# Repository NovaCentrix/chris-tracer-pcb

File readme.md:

# The TraceR 

## A Module for Simulating Conductive Ink PCB Traces

## Revisions

### Version 2

* Digipot power supply from from 3.3 to 5, in order to reduce the wiper
  resistance further (see the datasheet). This means the addition of
  level translator for the MISO signal into the MCU. 

* The digipot SDO pin is open drain. Added pullup resistors on each one.

* Assembly of modules onto v1 board was difficult. And the whole assembly 
  needs to be thinner so two modules can be installed adjacent to each
  other (relates to the pin header spacing on the main board). Gave up
  on the idea of avoiding a board cutout. Re-routing of signals, and
  made the board just slightly larger (mostly taller) to allow for the
  required cutout.

* Changed PCB thickness from 1.6 to 1.0 mm.

* Found some tiny buttons (about the same size as those on the Tiny 2040
  module) and put them at the top corners. This will allow the user to
  change resistance values without using the serial port.

### Version 1

First release. 

## Observations

Before I forget, here are some thoughts to consider if there ever is
going to be a version 3.

* Make D1/D2 larger, since that package is nearly impossible to hand
  solder. Or...

* Make the transistor and resistor packages smaller and reflow rather
  than hand solder. Also, Digipots are available in a smaller package:
    * TSSOP-24 package 7.8 x 4.4 mm 
    * SOIC-24W 15.4 x 7.5 mm (currently used)

* Look carefully at the Adafruit Qt Py RP2040 module. It looks smaller,
  has a smaller and well-defined required cutout and mechanical
  drawings. Fewer pins.

* Save even more space my tossing the module concept and building the
  RP2040 board and the OLED module directly on the TraceR's PCB.

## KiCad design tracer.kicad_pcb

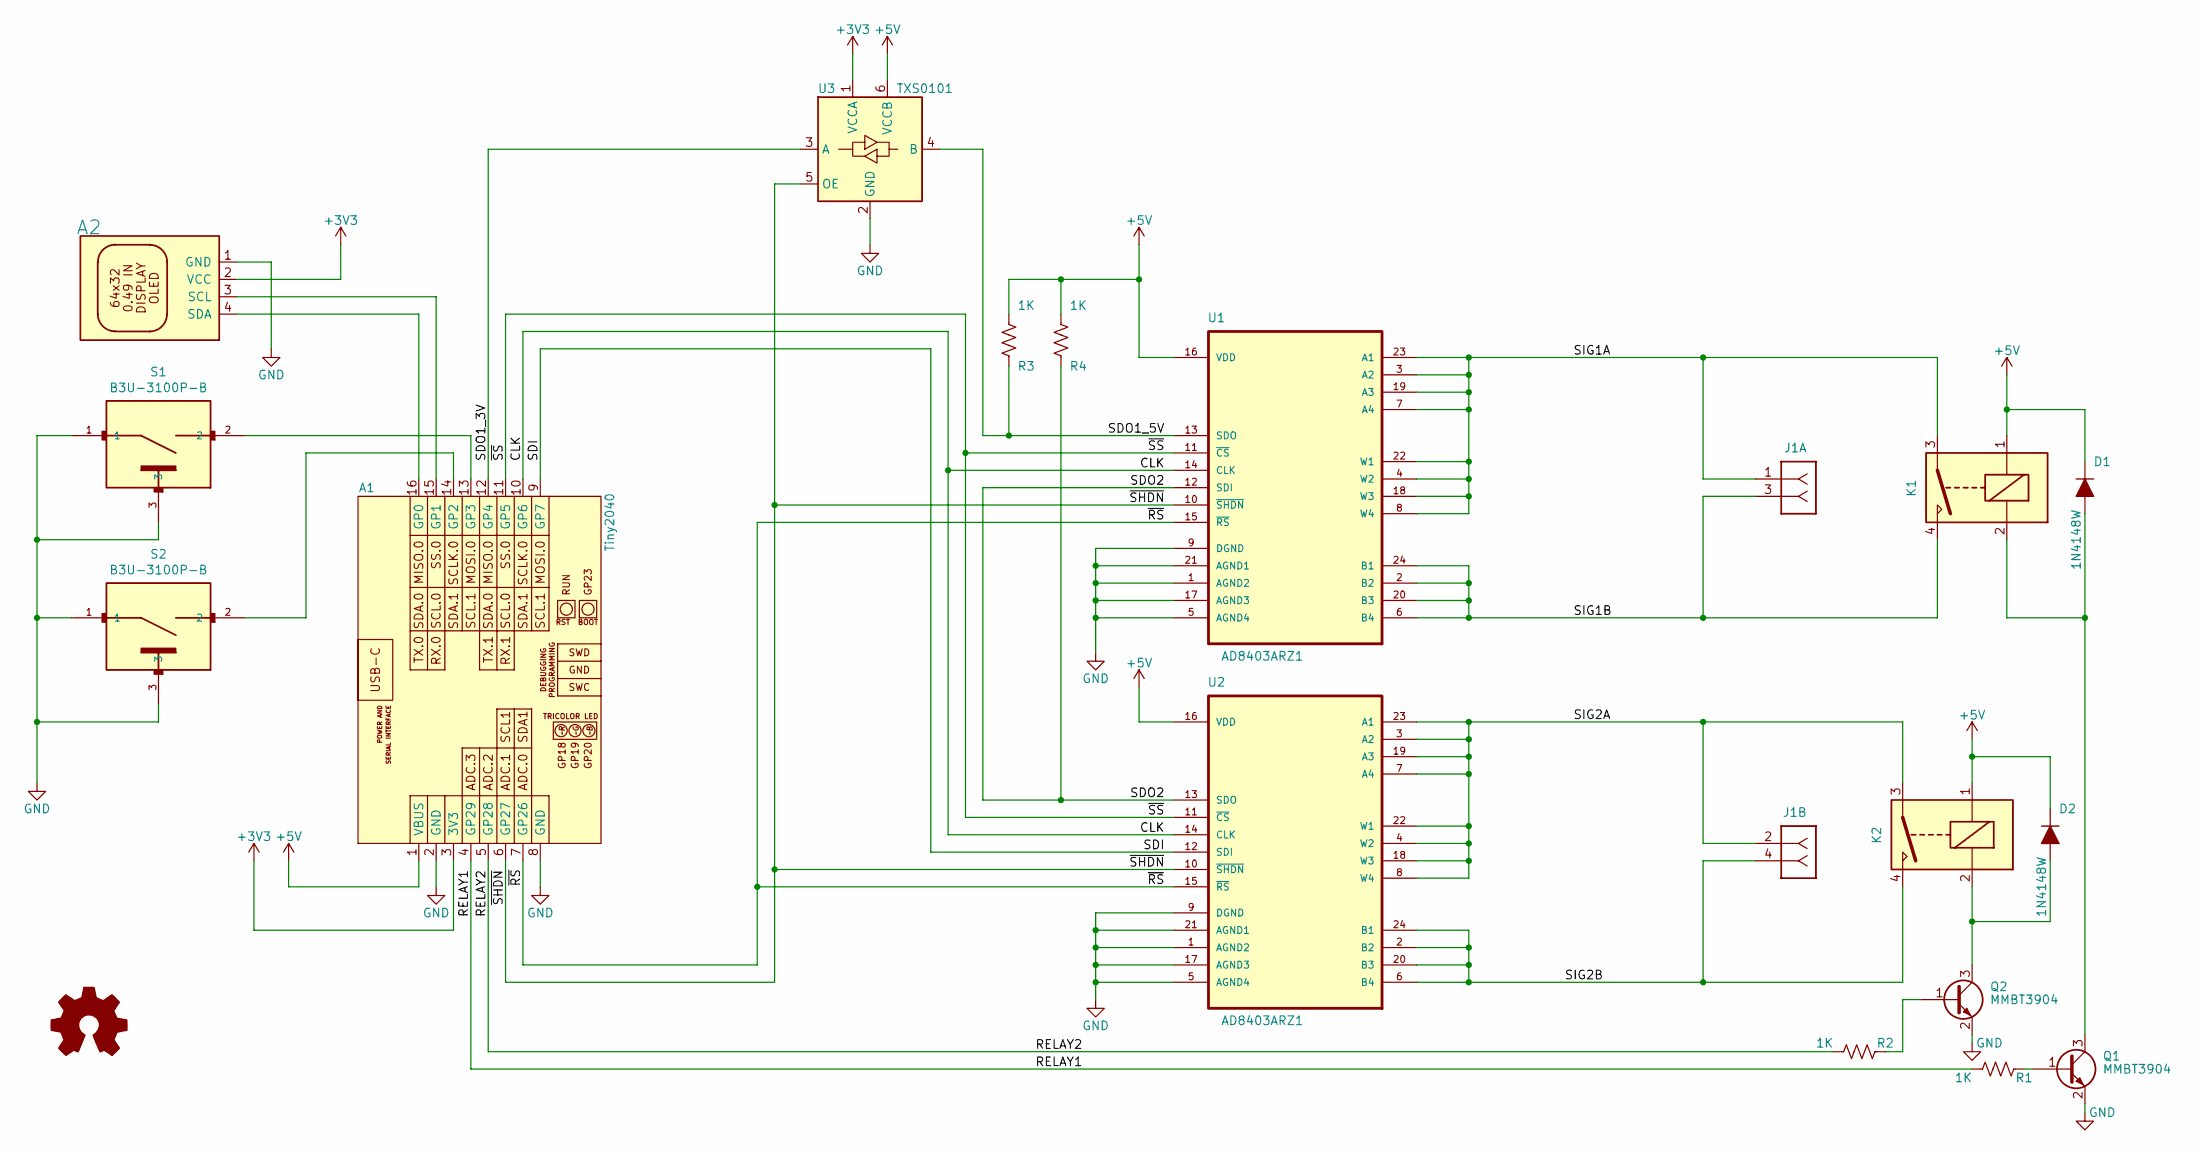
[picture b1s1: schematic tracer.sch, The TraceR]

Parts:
A1: Tiny2040; MODULE_TINY_2040_DEV2
A2: ASSY_OLED_490MILS_62x32_I2C; MODULE_OLED_490_SMALL_PADS
D1, D2: 1N4148W; DFN1006-2
J1: IO_JACK_F04_SPLIT; SAMTEC-SSQ-102-02-SIDEWAYS
K1, K2: Coto-9913-05-20; REED_RELAY_COTO_9913
LOGO1: Logo_Open_Hardware_Small; OSHW-Logo2_7.3x6mm_SilkScreen
Q1, Q2: MMBT3904; SOT-23
R1, R2, R3, R4: 1K; R_0805_2012Metric
S1, S2: B3U-3100P-B; SW_B3U-3100P-B
U1, U2: AD8403ARZ1; SOIC-24W_7.5x15.4mm_P1.27mm
U3: TXS0101; SOT-23-6

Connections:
+3V3: A1.3 (3V3), A2.2 (VCC), U3.1 (VCCA)
+5V: A1.1 (VBUS), D1.1 (K), D2.1 (K), K1.1, K2.1, R3.2, R4.2, U1.16 (VDD), U2.16 (VDD), U3.6 (VCCB)
/CLK: A1.10 (GP6), U1.14 (CLK), U2.14 (CLK)
/RELAY1: A1.4 (GP29), R1.2
/RELAY2: A1.5 (GP28), R2.2
/SDI: A1.9 (GP7), U2.12 (SDI)
/SDO1_3V: A1.12 (GP4), U3.3 (A)
/SDO1_5V: R3.1, U1.13 (SDO), U3.4 (B)
/SDO2: R4.1, U1.12 (SDI), U2.13 (SDO)
/SIG1A: J1.1, K1.3, U1.3 (A2), U1.4 (W2), U1.7 (A4), U1.8 (W4), U1.18 (W3), U1.19 (A3), U1.22 (W1), U1.23 (A1)
/SIG1B: J1.3, K1.4, U1.2 (B2), U1.6 (B4), U1.20 (B3), U1.24 (B1)
/SIG2A: J1.2, K2.3, U2.3 (A2), U2.4 (W2), U2.7 (A4), U2.8 (W4), U2.18 (W3), U2.19 (A3), U2.22 (W1), U2.23 (A1)
/SIG2B: J1.4, K2.4, U2.2 (B2), U2.6 (B4), U2.20 (B3), U2.24 (B1)
/~RS: A1.7 (GP26), U1.15 (~RS), U2.15 (~RS)
/~SHDN: A1.6 (GP27), U1.10 (~SHDN), U2.10 (~SHDN), U3.5 (OE)
/~SS: A1.11 (GP5), U1.11 (~CS), U2.11 (~CS)
GND: A1.2 (GND), A1.8 (GND), A2.1 (GND), Q1.2 (E), Q2.2 (E), S1.1, S1.3, S2.1, S2.3, U1.1 (AGND2), U1.5 (AGND4), U1.9 (DGND), U1.17 (AGND3), U1.21 (AGND1), U2.1 (AGND2), U2.5 (AGND4), U2.9 (DGND), U2.17 (AGND3), U2.21 (AGND1), U3.2 (GND)
unnamed 17: A1.13 (GP3), S1.2; also elsewhere on the board
unnamed 18: A1.14 (GP2), S2.2; also elsewhere on the board
unnamed: A1.15 (GP1), A2.3 (SCL)
unnamed: A1.16 (GP0), A2.4 (SDA)
unnamed: D1.2 (A), K1.2, Q1.3 (C)
unnamed: D2.2 (A), K2.2, Q2.3 (C)
unnamed: Q1.1 (B), R1.1
unnamed: Q2.1 (B), R2.1

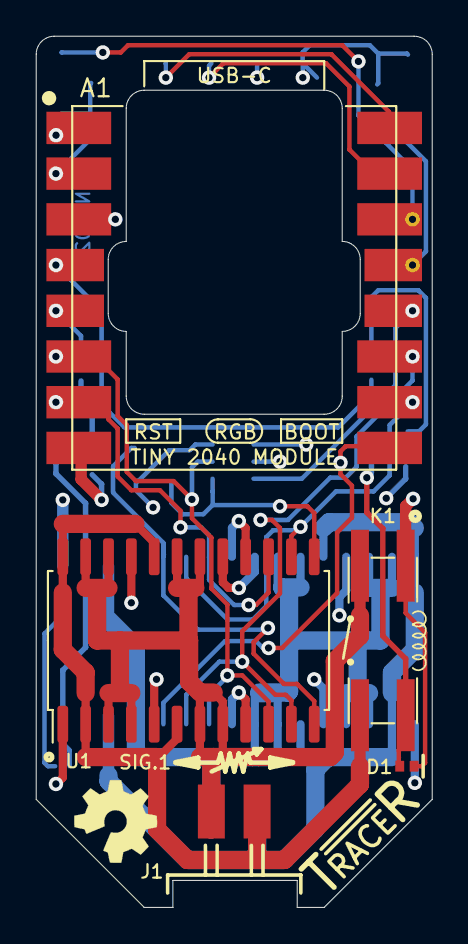
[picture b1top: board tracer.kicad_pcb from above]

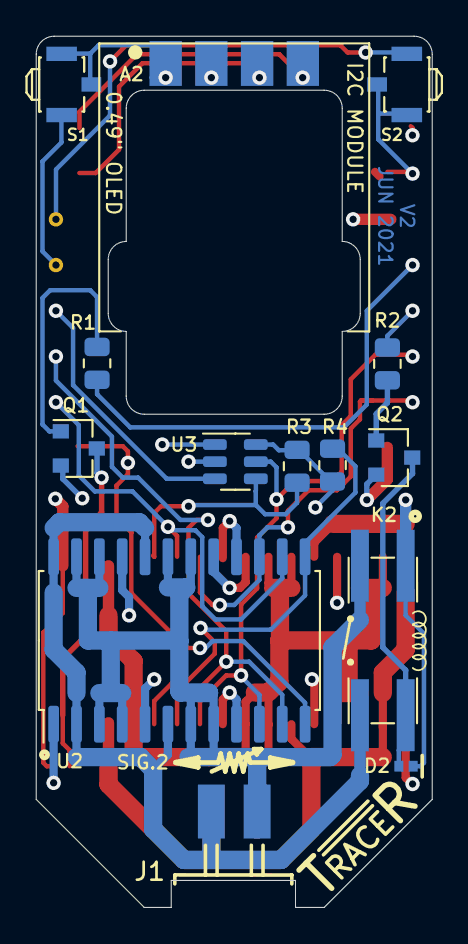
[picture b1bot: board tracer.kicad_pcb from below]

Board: 4 copper layers, 22.0 x 48.4 mm, 21 parts (13 on the bottom side), 25 nets.

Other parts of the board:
TP13, TP14: TestPoint; via-0.8x0.4

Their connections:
unnamed 17: TP13.1; also elsewhere on the board
unnamed 18: TP14.1; also elsewhere on the board

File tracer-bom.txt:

Reference	 Quantity	 Value	 Footprint	 Datasheet	 MANUFACTURER
A1 	1	"Tiny2040"	".tracer:MODULE_TINY_2040_DEV2"	""
A2 	1	"ASSY_OLED_490MILS_62x32_I2C"	".tracer:MODULE_OLED_490_SMALL_PADS"	""
U1 U2 	2	"AD8403ARZ1"	".tracer:SOIC-24W_7.5x15.4mm_P1.27mm"	""
U3 	1	"TXS0101"	".tracer:SOT-23-6"	""
Q1 Q2 	2	"MMBT3904"	".tracer:SOT-23"	"https://www.onsemi.com/pub/Collateral/2N3903-D.PDF"
D1 D2 	2	"1N4148W"	".tracer:DFN1006-2"	""
R1 R2 R3 R4 	4	"1K"	".tracer:R_0805_2012Metric"	""
K1 K2 	2	"Coto-9913-05-20"	".tracer:REED_RELAY_COTO_9913"	""
S1 S2 	2	"B3U-3100P-B"	".tracer:SW_B3U-3100P-B"	""	"Omron"
J1 	1	"IO_JACK_F04_SPLIT"	".tracer:SAMTEC-SSQ-102-02-SIDEWAYS"	""

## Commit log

2021-05-20 initial release, version 1 PCB
2021-05-20 Made Project Self-contained
2021-05-20 added readme.md
2021-05-20 added schematic printouts
2021-05-23 updated 3D views
2021-05-23 notes for v2
2021-05-24 changes for 5V/3.3V SDI
2021-06-13 v2 release to PCB shop
2021-06-14 documentation updates
2021-06-14 readme edit
2021-06-15 updating BOM
